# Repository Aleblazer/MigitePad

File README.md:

# MigitePad
## *__MigitePad!__* A Numpad/Nav Cluster with QMK Firmware/Kailh Hotswap/OLED/Rotary Encoder! 

Even reversable for you crazies who want a backwards Numpad!*
*OLED will need to be trace cut and bodged if you want it to work backwards

Materials needed:
* 30x Kailh Hotswap Sockets (Technically optional, hotswap through holes are plated)
* 31x 1N4148 or SOD-123F Diodes
* 30x MX style switches
* 1x MJTP1117 Reset Switch
* 1x Pro Micro or equivilant (Pro Micro chip side up for normal orientation, bottom side up for reversed.)
* 3x 2u stabilizers
* 1x EC11 Rotary Encoder
* 1x SSD1306 OLED (Optional)

For the 3D Printable Case:
* 6x 6mm M2 standoffs
* 12x M2 4mm or 5mm screws

OLED and Rotary Encoder code would need to be added to the end of your keymap.c. Still working on a more official OLED config. Example code borrowed and tested as working from the RoMac+, and is located in "QMK Keyboard Folder/migitepad/keymaps/default/keymap.c". Also encluded a default hex file in the QMK Keyboard Folder.

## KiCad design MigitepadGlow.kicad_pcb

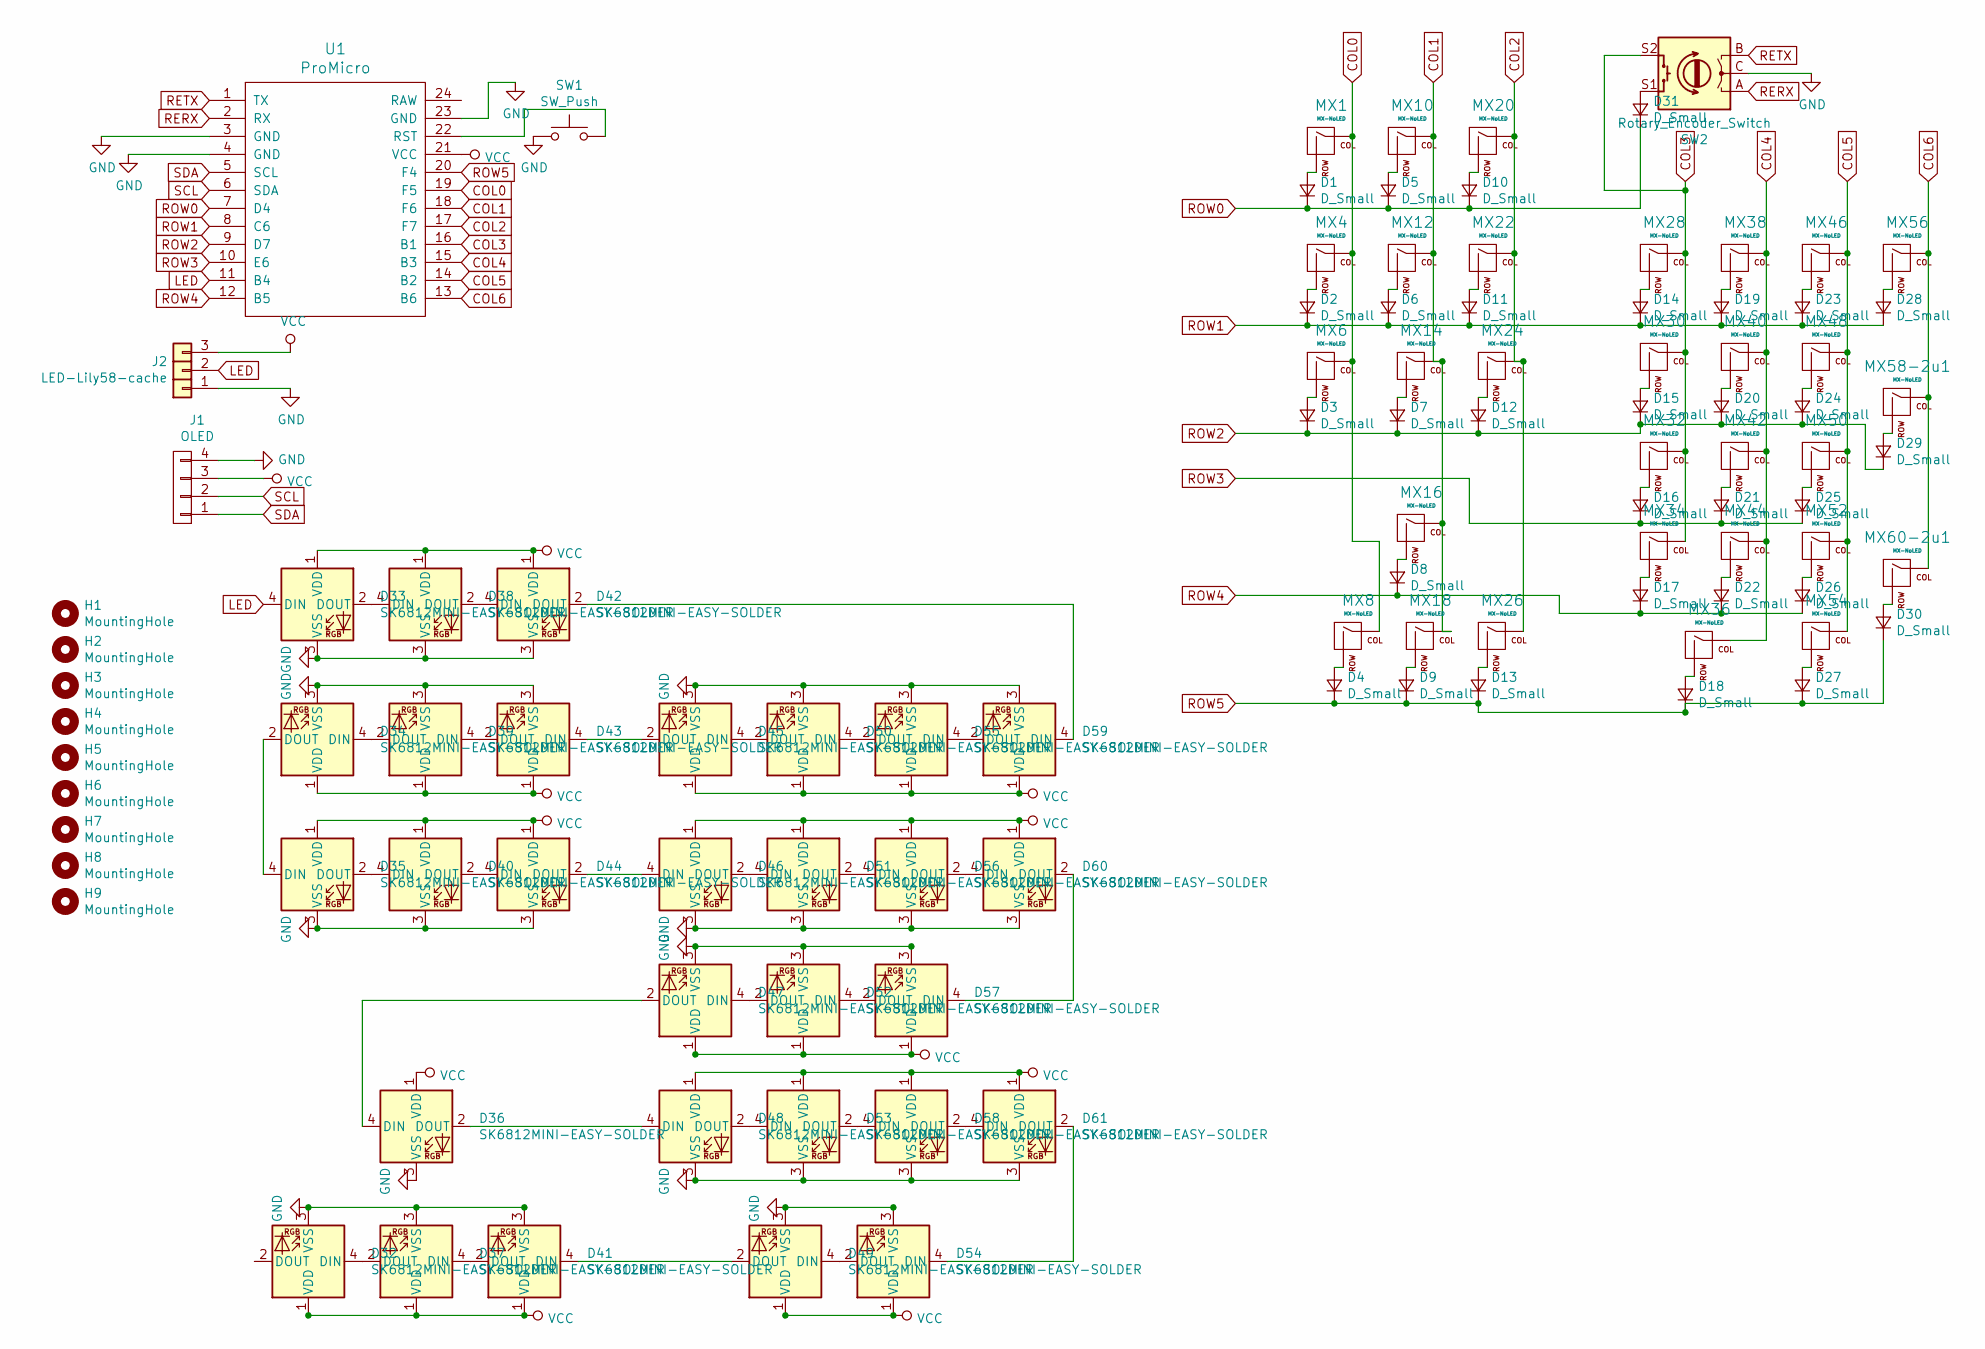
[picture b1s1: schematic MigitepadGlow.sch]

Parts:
D1, D2, D3, D4, D5, D6, D7, D8, D9, D10, D11, D12, D13, D14, D15, D16, D17, D18, D19, D20, D21, D22, D23, D24, D25, D26, D27, D28, D29, D30, D31: D_Small; Diode_TH_SOD123
D32, D33, D34, D35, D36, D37, D38, D39, D40, D41, D42, D43, D44, D45, D46, D47, D48, D49, D50, D51, D52, D53, D54, D55, D56, D57, D58, D59, D60, D61: SK6812MINI-EASY-SOLDER; YS-SK6812MINI-E
H1, H2, H3: MountingHole; Stabilizer_MX_2u
H4, H5, H6, H7, H8, H9: MountingHole; HOLE_M2_TH
J1: OLED; MY_SIL-4
J2: LED-Lily58-cache; LED
MX1, MX4, MX6, MX8, MX10, MX12, MX14, MX16, MX18, MX20, MX22, MX24, MX26, MX28, MX30, MX32, MX34, MX36, MX38, MX40, MX42, MX44, MX46, MX48, MX50, MX52, MX54, MX56, MX58-2u1, MX60-2u1: MX-NoLED; MXOnly-1U-Hotswap-Double-noled
SW1: SW_Push; SW_Tactile_SPST_Angled_MJTP1117
SW2: Rotary_Encoder_Switch; RotaryEncoder_EC11
U1: ProMicro

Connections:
COL0: MX1.1 (COL), MX4.1 (COL), MX6.1 (COL), MX8.1 (COL), U1.19 (F5)
COL1: MX10.1 (COL), MX12.1 (COL), MX14.1 (COL), MX16.1 (COL), MX18.1 (COL), U1.18 (F6)
COL2: MX20.1 (COL), MX22.1 (COL), MX24.1 (COL), MX26.1 (COL), U1.17 (F7)
COL3: MX28.1 (COL), MX30.1 (COL), MX32.1 (COL), MX34.1 (COL), SW2.S2, U1.16 (B1)
COL4: MX36.1 (COL), MX38.1 (COL), MX40.1 (COL), MX42.1 (COL), MX44.1 (COL), U1.15 (B3)
COL5: MX46.1 (COL), MX48.1 (COL), MX50.1 (COL), MX52.1 (COL), MX54.1 (COL), U1.14 (B2)
COL6: MX56.1 (COL), MX58-2u1.1 (COL), MX60-2u1.1 (COL), U1.13 (B6)
GND: D32.3 (VSS), D33.3 (VSS), D34.3 (VSS), D35.3 (VSS), D36.3 (VSS), D37.3 (VSS), D38.3 (VSS), D39.3 (VSS), D40.3 (VSS), D41.3 (VSS), D42.3 (VSS), D43.3 (VSS), D44.3 (VSS), D45.3 (VSS), D46.3 (VSS), D47.3 (VSS), D48.3 (VSS), D49.3 (VSS), D50.3 (VSS), D51.3 (VSS), D52.3 (VSS), D53.3 (VSS), D54.3 (VSS), D55.3 (VSS), D56.3 (VSS), D57.3 (VSS), D58.3 (VSS), D59.3 (VSS), D60.3 (VSS), D61.3 (VSS), J1.4, J2.1, SW1.1, SW2.C, U1.3 (GND), U1.4 (GND), U1.23 (GND)
LED: D33.4 (DIN), J2.2, U1.11 (B4)
unnamed: D1.2 (A), MX1.2 (ROW)
unnamed: D2.2 (A), MX4.2 (ROW)
unnamed: D3.2 (A), MX6.2 (ROW)
unnamed: D4.2 (A), MX8.2 (ROW)
unnamed: D5.2 (A), MX10.2 (ROW)
unnamed: D6.2 (A), MX12.2 (ROW)
unnamed: D7.2 (A), MX14.2 (ROW)
unnamed: D8.2 (A), MX16.2 (ROW)
unnamed: D9.2 (A), MX18.2 (ROW)
unnamed: D10.2 (A), MX20.2 (ROW)
unnamed: D11.2 (A), MX22.2 (ROW)
unnamed: D12.2 (A), MX24.2 (ROW)
unnamed: D13.2 (A), MX26.2 (ROW)
unnamed: D14.2 (A), MX28.2 (ROW)
unnamed: D15.2 (A), MX30.2 (ROW)
unnamed: D16.2 (A), MX32.2 (ROW)
unnamed: D17.2 (A), MX34.2 (ROW)
unnamed: D18.2 (A), MX36.2 (ROW)
unnamed: D19.2 (A), MX38.2 (ROW)
unnamed: D20.2 (A), MX40.2 (ROW)
unnamed: D21.2 (A), MX42.2 (ROW)
unnamed: D22.2 (A), MX44.2 (ROW)
unnamed: D23.2 (A), MX46.2 (ROW)
unnamed: D24.2 (A), MX48.2 (ROW)
unnamed: D25.2 (A), MX50.2 (ROW)
unnamed: D26.2 (A), MX52.2 (ROW)
unnamed: D27.2 (A), MX54.2 (ROW)
unnamed: D28.2 (A), MX56.2 (ROW)
unnamed: D29.2 (A), MX58-2u1.2 (ROW)
unnamed: D30.2 (A), MX60-2u1.2 (ROW)
unnamed: D31.2 (A), SW2.S1
unnamed: D32.4 (DIN), D37.2 (DOUT)
unnamed: D33.2 (DOUT), D38.4 (DIN)
unnamed: D34.2 (DOUT), D35.4 (DIN)
unnamed: D34.4 (DIN), D39.2 (DOUT)
unnamed: D35.2 (DOUT), D40.4 (DIN)
unnamed: D36.2 (DOUT), D48.4 (DIN)
unnamed: D36.4 (DIN), D47.2 (DOUT)
unnamed: D37.4 (DIN), D41.2 (DOUT)
unnamed: D38.2 (DOUT), D42.4 (DIN)
unnamed: D39.4 (DIN), D43.2 (DOUT)
unnamed: D40.2 (DOUT), D44.4 (DIN)
unnamed: D41.4 (DIN), D49.2 (DOUT)
unnamed: D42.2 (DOUT), D59.4 (DIN)
unnamed: D43.4 (DIN), D45.2 (DOUT)
unnamed: D44.2 (DOUT), D46.4 (DIN)
unnamed: D45.4 (DIN), D50.2 (DOUT)
unnamed: D46.2 (DOUT), D51.4 (DIN)
unnamed: D47.4 (DIN), D52.2 (DOUT)
unnamed: D48.2 (DOUT), D53.4 (DIN)
unnamed: D49.4 (DIN), D54.2 (DOUT)
unnamed: D50.4 (DIN), D55.2 (DOUT)
unnamed: D51.2 (DOUT), D56.4 (DIN)
unnamed: D52.4 (DIN), D57.2 (DOUT)
unnamed: D53.2 (DOUT), D58.4 (DIN)
unnamed: D54.4 (DIN), D61.2 (DOUT)
unnamed: D55.4 (DIN), D59.2 (DOUT)
unnamed: D56.2 (DOUT), D60.4 (DIN)
unnamed: D57.4 (DIN), D60.2 (DOUT)
unnamed: D58.2 (DOUT), D61.4 (DIN)
unnamed: SW1.2, U1.22 (RST)
RERX: SW2.A, U1.2 (RX)
RETX: SW2.B, U1.1 (TX)
ROW0: D1.1 (K), D5.1 (K), D10.1 (K), D31.1 (K), U1.7 (D4)
ROW1: D2.1 (K), D6.1 (K), D11.1 (K), D14.1 (K), D19.1 (K), D23.1 (K), D28.1 (K), U1.8 (C6)
ROW2: D3.1 (K), D7.1 (K), D12.1 (K), D15.1 (K), D20.1 (K), D24.1 (K), D29.1 (K), U1.9 (D7)
ROW3: D16.1 (K), D21.1 (K), D25.1 (K), U1.10 (E6)
ROW4: D8.1 (K), D17.1 (K), D22.1 (K), D26.1 (K), U1.12 (B5)
ROW5: D4.1 (K), D9.1 (K), D13.1 (K), D18.1 (K), D27.1 (K), D30.1 (K), U1.20 (F4)
SCL: J1.2, U1.6 (SDA)
SDA: J1.1, U1.5 (SCL)
VCC: D32.1 (VDD), D33.1 (VDD), D34.1 (VDD), D35.1 (VDD), D36.1 (VDD), D37.1 (VDD), D38.1 (VDD), D39.1 (VDD), D40.1 (VDD), D41.1 (VDD), D42.1 (VDD), D43.1 (VDD), D44.1 (VDD), D45.1 (VDD), D46.1 (VDD), D47.1 (VDD), D48.1 (VDD), D49.1 (VDD), D50.1 (VDD), D51.1 (VDD), D52.1 (VDD), D53.1 (VDD), D54.1 (VDD), D55.1 (VDD), D56.1 (VDD), D57.1 (VDD), D58.1 (VDD), D59.1 (VDD), D60.1 (VDD), D61.1 (VDD), J1.3, J2.3, U1.21 (VCC)

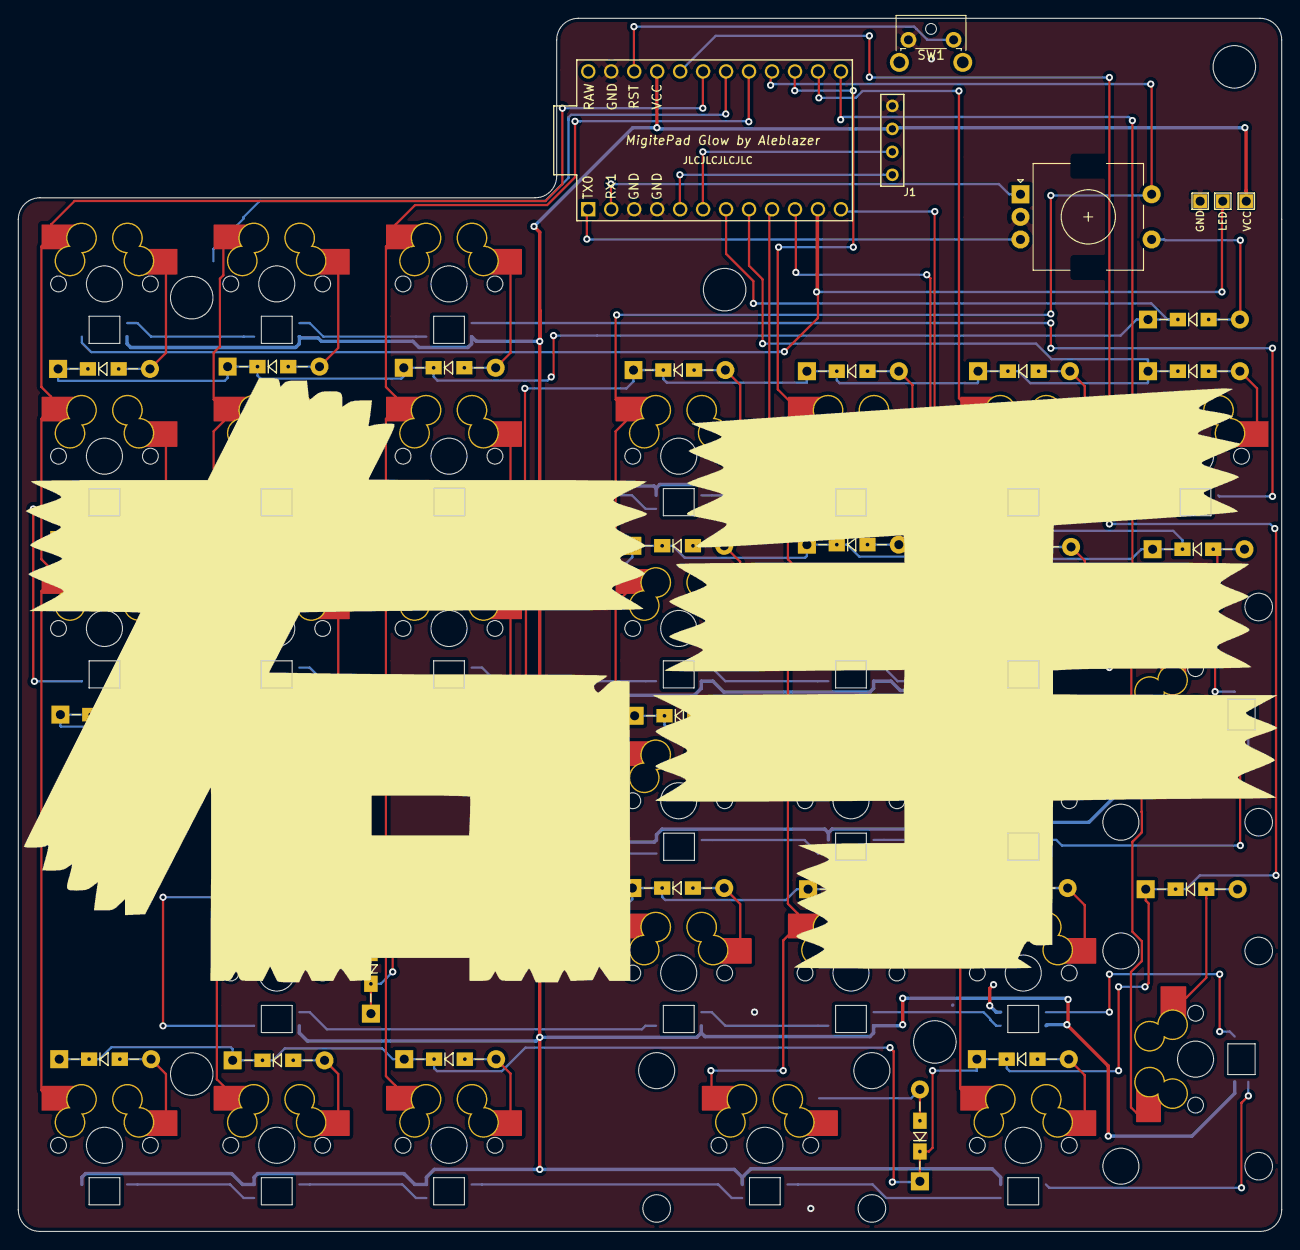
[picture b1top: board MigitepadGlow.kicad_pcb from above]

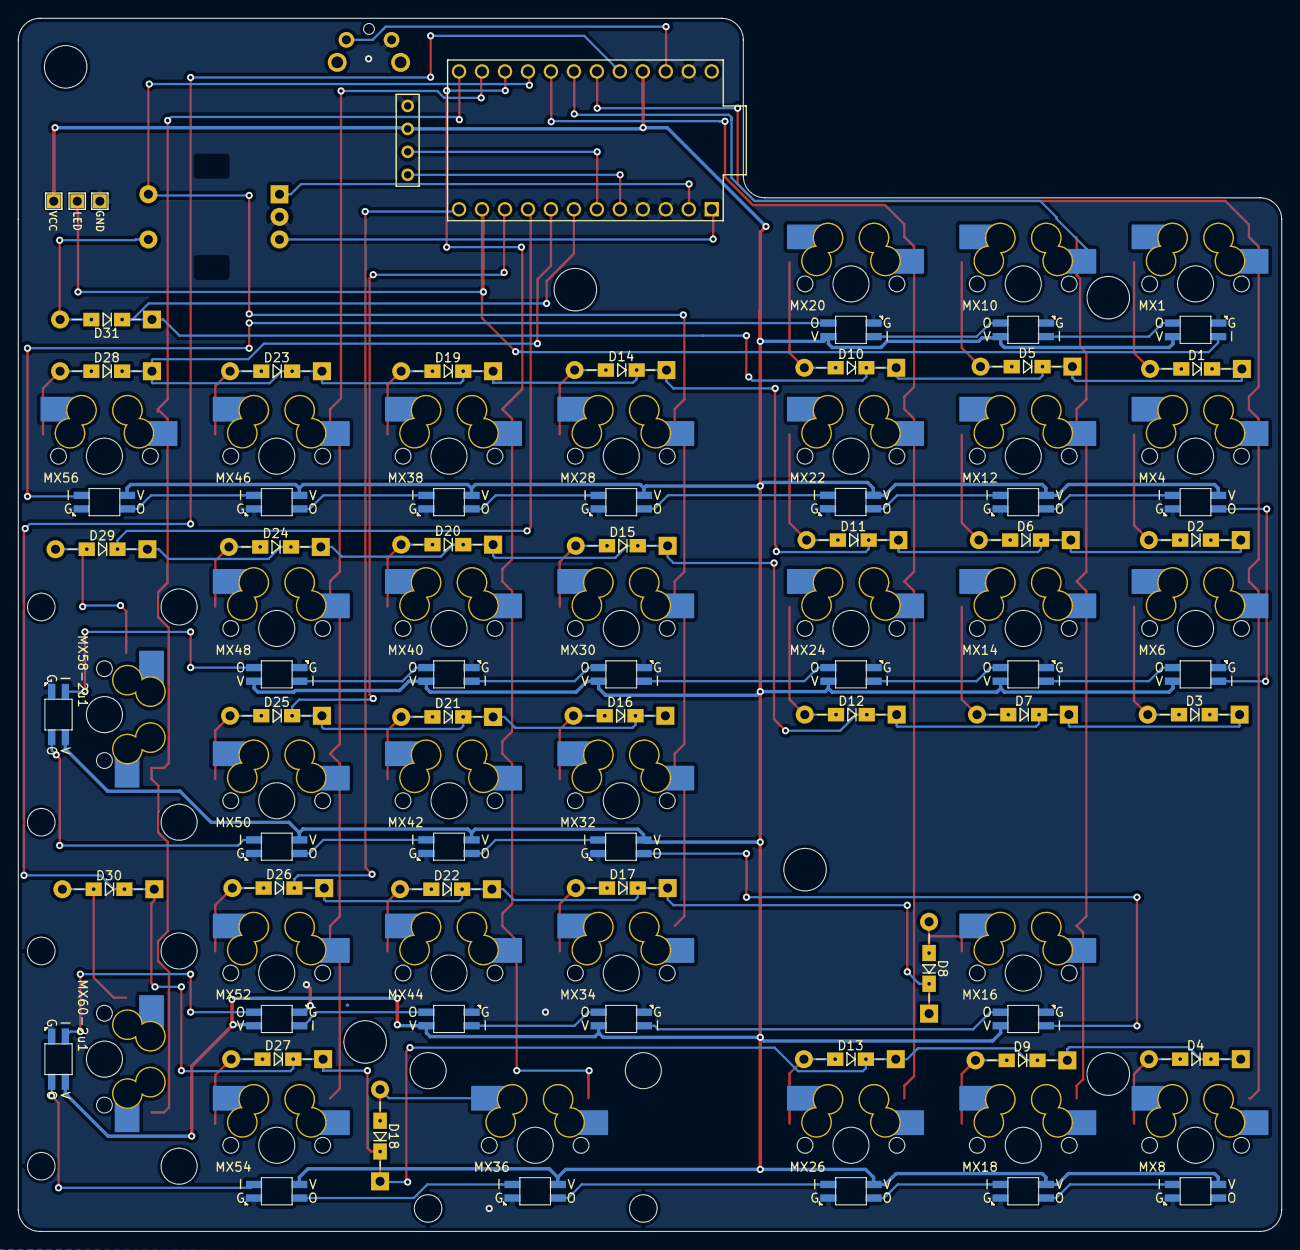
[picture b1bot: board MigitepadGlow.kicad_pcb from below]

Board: 2 copper layers, 139.7 x 134.1 mm, 105 parts (60 on the bottom side), 81 nets.

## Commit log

2020-02-24 Add submodules
2020-02-24 Added Footprints
2020-02-26 Draw the rest of the owl.
2020-02-26 Moved MCU
2020-03-02 Changed to ProMicro
2020-03-02 Removed GND fill
2020-03-02 Added OLED header
2020-03-03 Split into v05(Standard) and v07(Kailh Hotswap)
2020-03-07 Changed Footprints
2020-03-08 Added Rotary Encoder
2020-03-08 Correct Submodules
2020-03-09 Rewired Encoder
2020-03-14 Gerbers and final touches
2020-03-17 Corrected Col1 Trace
2020-03-26 Removed old Gerbers, fixed more traces
2020-03-26 Added 3D printable plates
2020-03-27 Corrected stab spacing
2020-04-02 Updated Gerbers and README.md
2020-04-02 Added QMK firmware folder and default Pro Micro hex file
2020-04-02 Added image
2020-04-02 Added more images
2020-04-02 Readme again
2020-09-23 Added Migitepad Glow
    Added SKMini-E LEDs
2020-12-11 Updated QMK folder
2020-12-11 Keymap fix
2021-02-25 MigitePadGlow Final touches
